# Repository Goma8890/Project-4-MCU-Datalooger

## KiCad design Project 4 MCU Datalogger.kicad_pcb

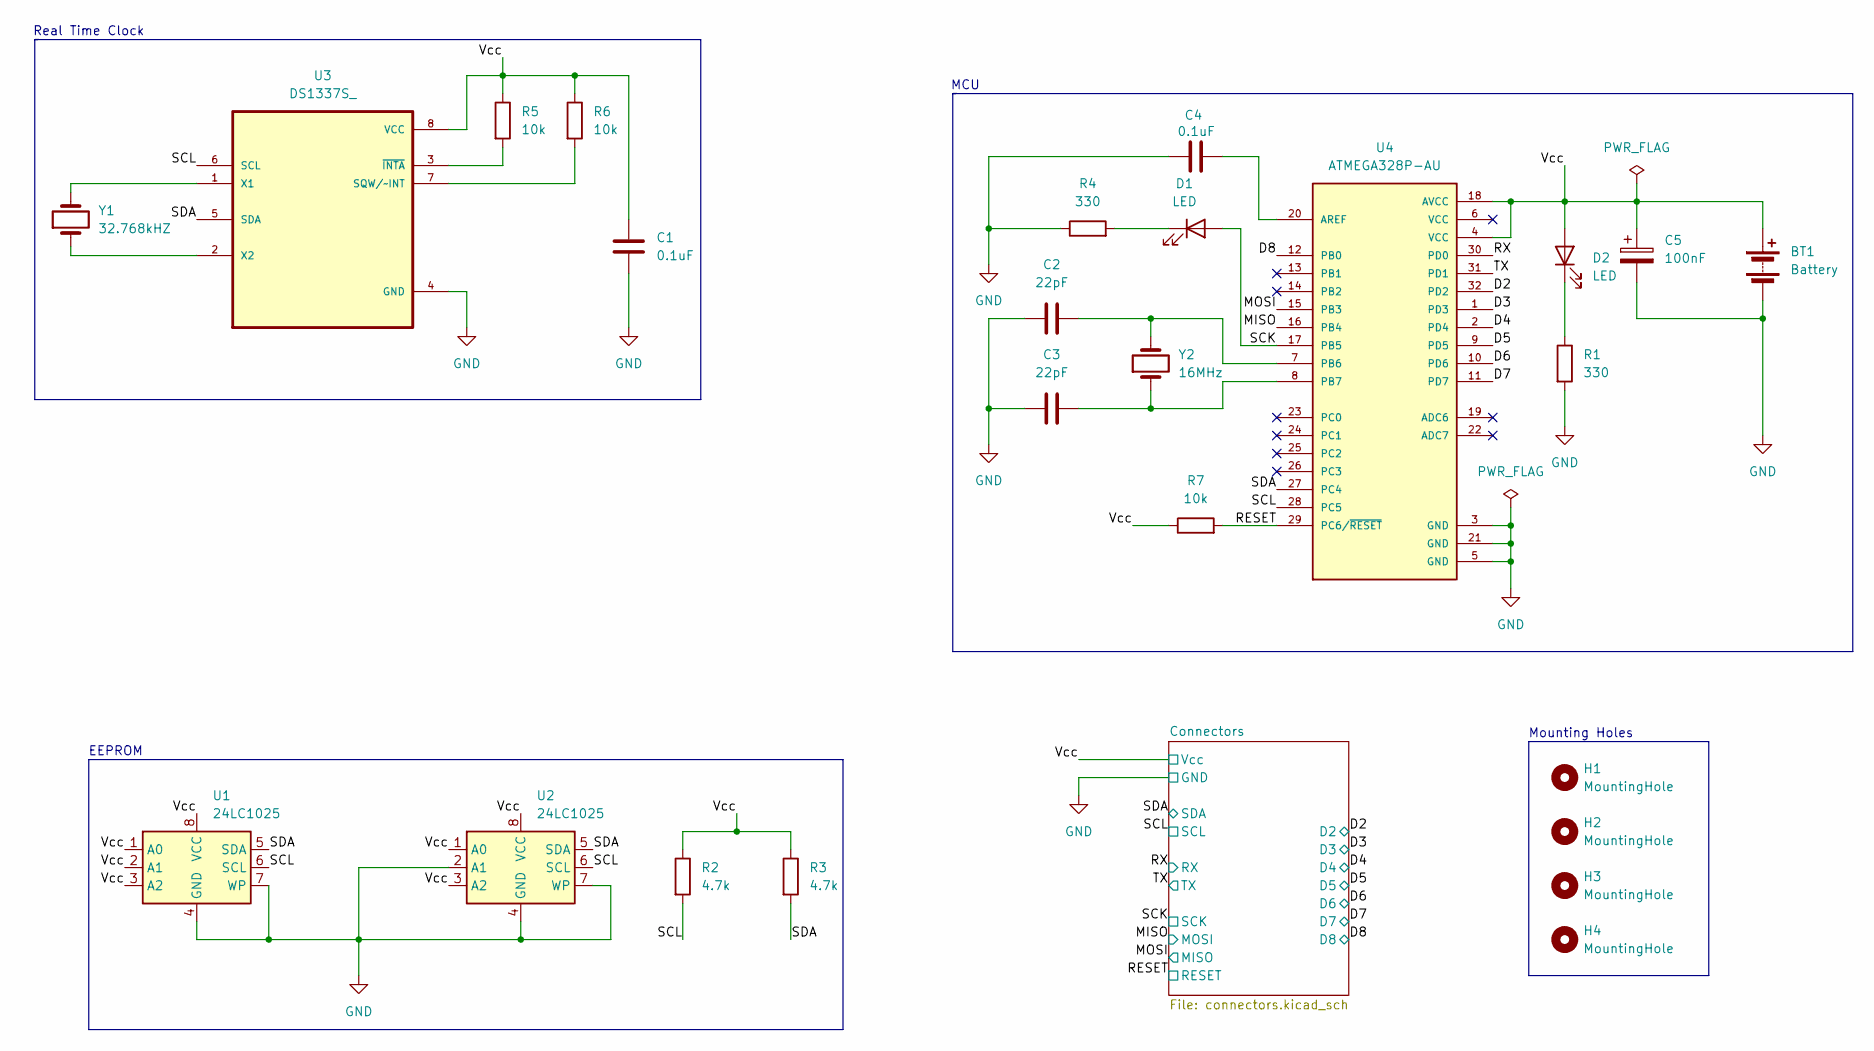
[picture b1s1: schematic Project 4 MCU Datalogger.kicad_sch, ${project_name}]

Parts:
BT1: Battery; PinHeader_1x02_P2.54mm_Vertical
C1, C4: 0.1uF; C_0805_2012Metric
C2, C3: 22pF; C_0805_2012Metric
C5: 100nF; C_0805_2012Metric
D1, D2: LED; LED_0805_2012Metric
H1, H2, H3, H4: MountingHole; MountingHole_2.1mm
R1, R4: 330; R_0805_2012Metric
R2, R3: 4.7k; R_0805_2012Metric
R5, R6, R7: 10k; R_0805_2012Metric
U1, U2: 24LC1025; SOIC-8_5.3x5.3mm_P1.27mm
U3: DS1337S_; SOIC127P600X175-8N
U4: ATMEGA328P-AU; QFP80P900X900X120-32N; PARTREV 8271A
Y1: 32.768kHZ; Crystal_SMD_5032-2Pin_5.0x3.2mm
Y2: 16MHz; Crystal_SMD_5032-2Pin_5.0x3.2mm

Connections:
/D2: U4.32 (PD2); also elsewhere on the board
/D3: U4.1 (PD3); also elsewhere on the board
/D4: U4.2 (PD4); also elsewhere on the board
/D5: U4.9 (PD5); also elsewhere on the board
/D6: U4.10 (PD6); also elsewhere on the board
/D7: U4.11 (PD7); also elsewhere on the board
/D8: U4.12 (PB0); also elsewhere on the board
/MISO: U4.16 (PB4); also elsewhere on the board
/MOSI: U4.15 (PB3); also elsewhere on the board
/RESET: R7.2, U4.29 (PC6/~RESET); also elsewhere on the board
/RX: U4.30 (PD0); also elsewhere on the board
/SCK: D1.2 (A), U4.17 (PB5); also elsewhere on the board
/SCL: R2.2, U1.6 (SCL), U2.6 (SCL), U3.6 (SCL), U4.28 (PC5); also elsewhere on the board
/SDA: R3.2, U1.5 (SDA), U2.5 (SDA), U3.5 (SDA), U4.27 (PC4); also elsewhere on the board
/TX: U4.31 (PD1); also elsewhere on the board
/Vcc: BT1.1 (+), C1.1, C5.1, D2.2 (A), R2.1, R3.1, R5.1, R6.1, R7.1, U1.1 (A0), U1.2 (A1), U1.3 (A2), U1.8 (VCC), U2.1 (A0), U2.3 (A2), U2.8 (VCC), U3.8 (VCC), U4.4 (VCC), U4.18 (AVCC); also elsewhere on the board
GND: BT1.2 (-), C1.2, C2.1, C3.1, C4.1, C5.2, R1.2, R4.1, U1.4 (GND), U1.7 (WP), U2.2 (A1), U2.4 (GND), U2.7 (WP), U3.4 (GND), U4.3 (GND), U4.5 (GND), U4.21 (GND); also elsewhere on the board
unnamed: D1.1 (K), R4.2
unnamed: D2.1 (K), R1.1
unnamed: R6.2, U3.7 (SQW/~INT)
unnamed: U3.1 (X1), Y1.2
unnamed: U3.2 (X2), Y1.1
unnamed: R5.2, U3.3 (~INTA)
unnamed: C4.2, U4.20 (AREF)
unnamed: C2.2, U4.7 (PB6), Y2.2
unnamed: C3.2, U4.8 (PB7), Y2.1

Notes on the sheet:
MCU
EEPROM
Mounting Holes
Real Time Clock

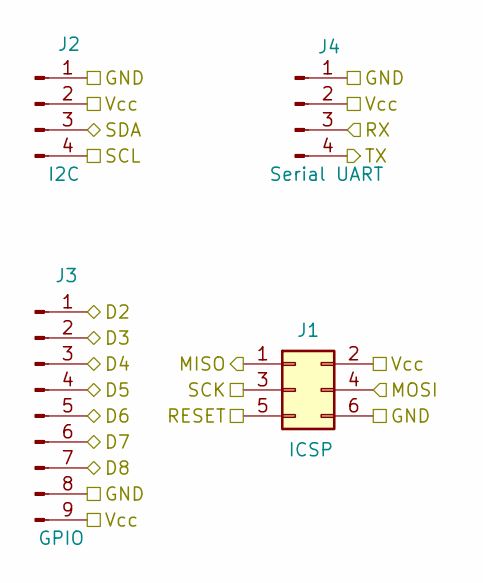
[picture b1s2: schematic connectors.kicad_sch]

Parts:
J1: Conn_02x03_Odd_Even; PinHeader_2x03_P2.54mm_Vertical
J2, J4: Conn_01x04_Pin; PinHeader_1x04_P2.54mm_Vertical
J3: Conn_01x09_Pin; PinHeader_1x09_P2.54mm_Vertical

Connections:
/D2: J3.1; also elsewhere on the board
/D3: J3.2; also elsewhere on the board
/D4: J3.3; also elsewhere on the board
/D5: J3.4; also elsewhere on the board
/D6: J3.5; also elsewhere on the board
/D7: J3.6; also elsewhere on the board
/D8: J3.7; also elsewhere on the board
/MISO: J1.4; also elsewhere on the board
/MOSI: J1.1; also elsewhere on the board
/RESET: J1.5; also elsewhere on the board
/RX: J4.3; also elsewhere on the board
/SCK: J1.3; also elsewhere on the board
/SCL: J2.4; also elsewhere on the board
/SDA: J2.3; also elsewhere on the board
/TX: J4.4; also elsewhere on the board
/Vcc: J1.2, J2.2, J3.9, J4.2; also elsewhere on the board
GND: J1.6, J2.1, J3.8, J4.1; also elsewhere on the board

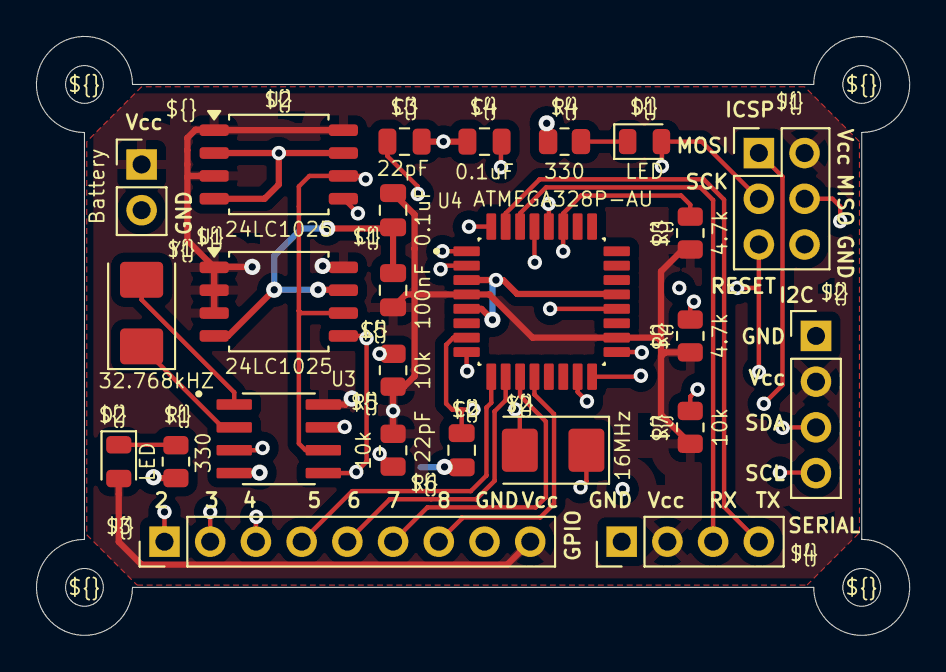
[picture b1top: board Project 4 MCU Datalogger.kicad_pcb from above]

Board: 4 copper layers, 48.5 x 33.3 mm, 29 parts (0 on the bottom side), 26 nets.

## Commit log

2025-11-02 First commit of new project
2025-11-02 Setup of EEschema of new project.
2025-11-02 Added required symbols to the schematic sheet.
2025-11-02 completed symbol-footprint association.
2025-11-02 Completed wiring in the second sheet.
2025-11-02 Allocated GND and Vcc nets to the Power net class.
2025-11-02 Completed Comments.
2025-11-03 Fixed some bugs.
2025-11-03 Setup Pcbnew.
2025-11-03 Placed footprints on the Pcbnew.
2025-11-04 Placed tracks on the Pcbnew.
2025-11-06 Wiring completed.
2025-11-06 Placed tracks in the Pcbnew.
2025-11-08 Fixed some issues.
2025-11-08 Fixed some issues again.
2025-11-08 Completed 2-layer Pcb project.
2025-11-08 Completed 2-layer Pcb.
2025-11-08 Added gerbers directories to gitignore.
2025-11-08 Added extra files to gitignore.
2025-11-08 Created the gerbers file.
2025-11-09 Completed 4 layer PCB.
2025-11-15 Added extra tracks.
2025-11-15 Edited extra files to gitignore.
2025-11-15 Committed changes.
2025-11-15 Delete 4_layer_MCU_Datalogger_Gerbers directory
    Delete files
2025-11-15 Delete 4_layer_MCU_Datalogger_Gerbers directory
    Deleted files
